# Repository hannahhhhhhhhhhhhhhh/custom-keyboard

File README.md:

# Custom keyboard - A  61-Key Mechanical Keyboard

A custom 60% keyboard that I designed from scratch in KiCad. It has 61 keys, runs on a Seeed XIAO nRF52840 Plus, connects over Bluetooth or USB-C, and uses RMK firmware so you can remap every key with Vial. :3
First time doing stuff with vial and rmk, it was quite a learning curve 

please excuse the lack of 3d models for the above image:  I couldn't add the STEP files to the 3D viewer because my computer keeps crashing when I go to the footprint editor trying to give it a model

## Why I Made This

Honestly, I wanted to design a whole keyboard myself instead of just buying one :D I'm still pretty new to PCB design, and a keyboard seemed like the best way to look at diode matrices, stabilizers other stuff and firmware. I picked the 60% layout because it keeps all the main keys without taking over my whole desk.

I started from the Hack Club Blueprint wireless keyboard guide, which builds a split keyboard. I adapted it into one single board, learned about how matrix worked, did the matrix for 61 keys and figuring out a LOT of pin stuff ;-; (more on that below).

## Specs

- **Layout:** 61-key 60% ANSI (2u Backspace, 2.25u Enter and Left Shift, 2.75u Right Shift, 6.25u Space)
- **Microcontroller:** Seeed XIAO nRF52840 Plus (surface mounted on the PCB)
- **Connectivity:** Bluetooth LE and USB-C
- **Switches:** MX-style, soldered in (no hotswap sockets oops)
- **Matrix:** 5 rows x 14 columns, with one diode per key
- **Stabilizers:** 5 PCB-mount stabilizers
- **Power:** single-cell LiPo soldered to the battery pads, charged over USB-C by the XIAO
- **Firmware:** RMK (Rust), configured with `keyboard.toml` and remappable with Vial
- **Designed in:** KiCad!!!

## How It Works

### The key matrix

A 61-key keyboard would need 61 pins , and no microcontroller has that many so im forced to learn matrix. So the keys are wired as a matrix of 5 rows and 14 columns, which only needs 19 pins. The firmware drives one column at a time and checks which rows see a signal, which tells it exactly which key is pressed.

Every switch has its own diode (SOD-123, the diode footprint from the guide). 

### Why the XIAO nRF52840 Plus

The matrix needs 19 GPIO pins, and the regular XIAO only has 11. The Plus adds extra pads on the back (D11 to D19), so it's the only XIAO that fits this design. It also has Bluetooth, USB-C and a LiPo charger built in, so I swapped to it halfway

Two pin things btw:
- **D16 is unused because** Seeed lists it as the battery voltage sensing pin, so I eventually decided to stay away from it instead of using it as a key column. This also means there's no battery percentage readout, which I'm fine with for now. I added it then had to remove it, which is also why on the pcb the wiring looked a little odd for col11
- **D14 and D15 are NFC pins** by default. The firmware turns on the `nfc-pins-as-gpio` feature so they work as normal key columns.

### Battery

TP1 (GND) and TP2 (VBAT) are the battery pads. Solder a single-cell LiPo to them and the XIAO charges it whenever USB-C is plugged in.

### The PCB

The board has 61 switch footprints in a standard 60% layout, 5 stabilizer footprints (Backspace, Enter, Left Shift, Right Shift and Space), 6 mounting holes, and the two battery pads. and ground plane

## Keymap

The default keymap has two layers. You can change everything in Vial, so this is just where it starts.

- **Base layer:** a standard ANSI 60% layout. Esc is in the top-left corner, and Fn is next to Right Alt.
- **Fn layer:** hold Fn for F1 to F12 on the number row, Fn + Backspace for Delete, Fn + Esc for the backtick, and the arrow keys on I, J, K and L.

## Bill of Materials

All prices are in USD. I'm Canadian, so most of my prices were in CAD and I converted them at about 1 CAD = 0.72 USD.

| Item | Qty | Supplier | Cost/Item (USD) | Total Cost (USD) | Link |
|------|-----|----------|-----------------|------------------|------|
| PCB | 1 | JLCPCB | $34.12 | $34.12 | [link](https://cart.jlcpcb.com/quote) |
| Seeed Studio XIAO nRF52840 Plus | 1 | RobotShop | $10.80 | $10.80 | [link](https://ca.robotshop.com/products/seeed-studio-xiao-nrf52840-plus) |
| YUNZII Milk V2 linear switches (35 per pack) | 2 | Canada Computers | $9.35 | $18.70 | [link](https://www.canadacomputers.com/en/keyboard-switches/285141/yunzii-milk-v2-linear-switch-35-pieces-per-pack-milk-v2.html) |
| ECSiNG stabilizer set (7x 2U and 1x 6.25U) | 1 | Amazon.ca | $9.50 | $9.50 | [link](https://www.amazon.ca/dp/B0FGHP1QQN) |
| SOD-123 diodes (ordered with the PCB) | 61 | JLCPCB | ordered with pcb | $0 | [link](https://cart.jlcpcb.com/quote) |
| Estimated total tax and shipping | 1 | | | $40.47 | |
| | | | **Total (before diodes)** | **$113.59** | |

same list but without the key switches cost is in [`BOM.csv`](BOM.csv). (I already bought the key switches myself so didn't count that in bom. Keycaps aren't in this list yet because I'm still deciding on a set, so they aren't in the total.

### About the shipping ;-;

ok so I have to explain the shipping because it looks kind of crazy. I'm Canadian, and almost every store I could order from charges around $20 in shipping per order, no matter how small the order is FOR SOME REASON. To avoid paying that yet again, I ordered the diodes together with the PCB from JLCPCB instead of buying them from another store. Even with that, the tax and shipping for the rest of the parts comes to about $40.47 CAD (around $29.14 USD), and that part was unavoidable. So over a quarter of my total is just shipping q-p

## Firmware Flashing Guide

The firmware is built with [RMK](https://rmk.rs) and lives in the `firmware/` folder: `keyboard.toml` has the pins, layout and keymap, and `vial.json` has the layout for Vial.

### What you need

- A USB-C **data** cable (some cables only charge)
- The firmware as a `.uf2` file (see step 1)

### 1. Get the firmware

**Option A: GitHub Actions ** 
1. Open the **Actions** tab of this repo.
2. Click the latest successful run.
3. Download the firmware from **Artifacts** and unzip it. The `.uf2` file is inside.

**Option B:just do it**
1. Install Rust and `cargo-make`: `cargo install --force cargo-make`
2. In the `firmware/` folder, run `cargo make uf2 --release`

### 2. Put the keyboard in bootloader mode

1. Plug the keyboard into your computer over USB-C.
2. **Double-tap** the small reset button on the XIAO, quickly.
3. A new USB drive appears on your computer.

### 3. Flash it

Drag the `.uf2` file onto the new drive. The drive disappears and the keyboard reboots. That's it, you're done! (If macOS shows an error while copying, you can ignore it.)

### 4. Connect

- **USB:** it works as soon as it's plugged in.
- **Bluetooth:** pair with **keyboard:3** in your computer's Bluetooth settings.
- **Remapping:** plug it in over USB and open Vial to change keys and layers.

### Troubleshooting

| Problem | Fix |
|---------|-----|
| The USB drive doesn't appear | Double-tap the reset button faster, and try a different USB-C cable (it must be a data cable). |
| Two columns of keys do nothing | Those are the NFC pins (COL7 and COL9). Make sure `nfc-pins-as-gpio` is enabled on the `embassy-nrf` dependency in `Cargo.toml`. |
| Keys type the wrong thing | Open Vial and check the keymap. The layout in `vial.json` has to match `keyboard.toml` tho. |

## What I Learned

- A diode matrix is way less scary than it looks :D
- Not every pin on a microcontroller is a normal GPIO pin
- Reading the ERC errors one by one is much better than panicking at the number ;-;
- Getting the pin names right across the schematic, the footprints, the firmware and Vial is the hardest part of the whole project :pain:

## Repository Structure

```
.
├── README.md
├── BOM.csv
├── images/
│   ├── schematic.png
│   ├── pcb.png
│   └── pcb-3d.png
├── kicad/
│   ├── keyboard.kicad_pro
│   ├── keyboard.kicad_sch
│   └── keyboard.kicad_pcb
├── production/
│   ├── keyboard.zip
│   ├── bom.csv
│   ├── positions.csv
│   └── netlist.ipc
├── firmware/
│   ├── Cargo.toml
│   ├── keyboard.toml
│   ├── main.rs
│   ├── memory.x
│   └── vial.json
└── .github/workflows/
```

## Made For

Hack Club :3

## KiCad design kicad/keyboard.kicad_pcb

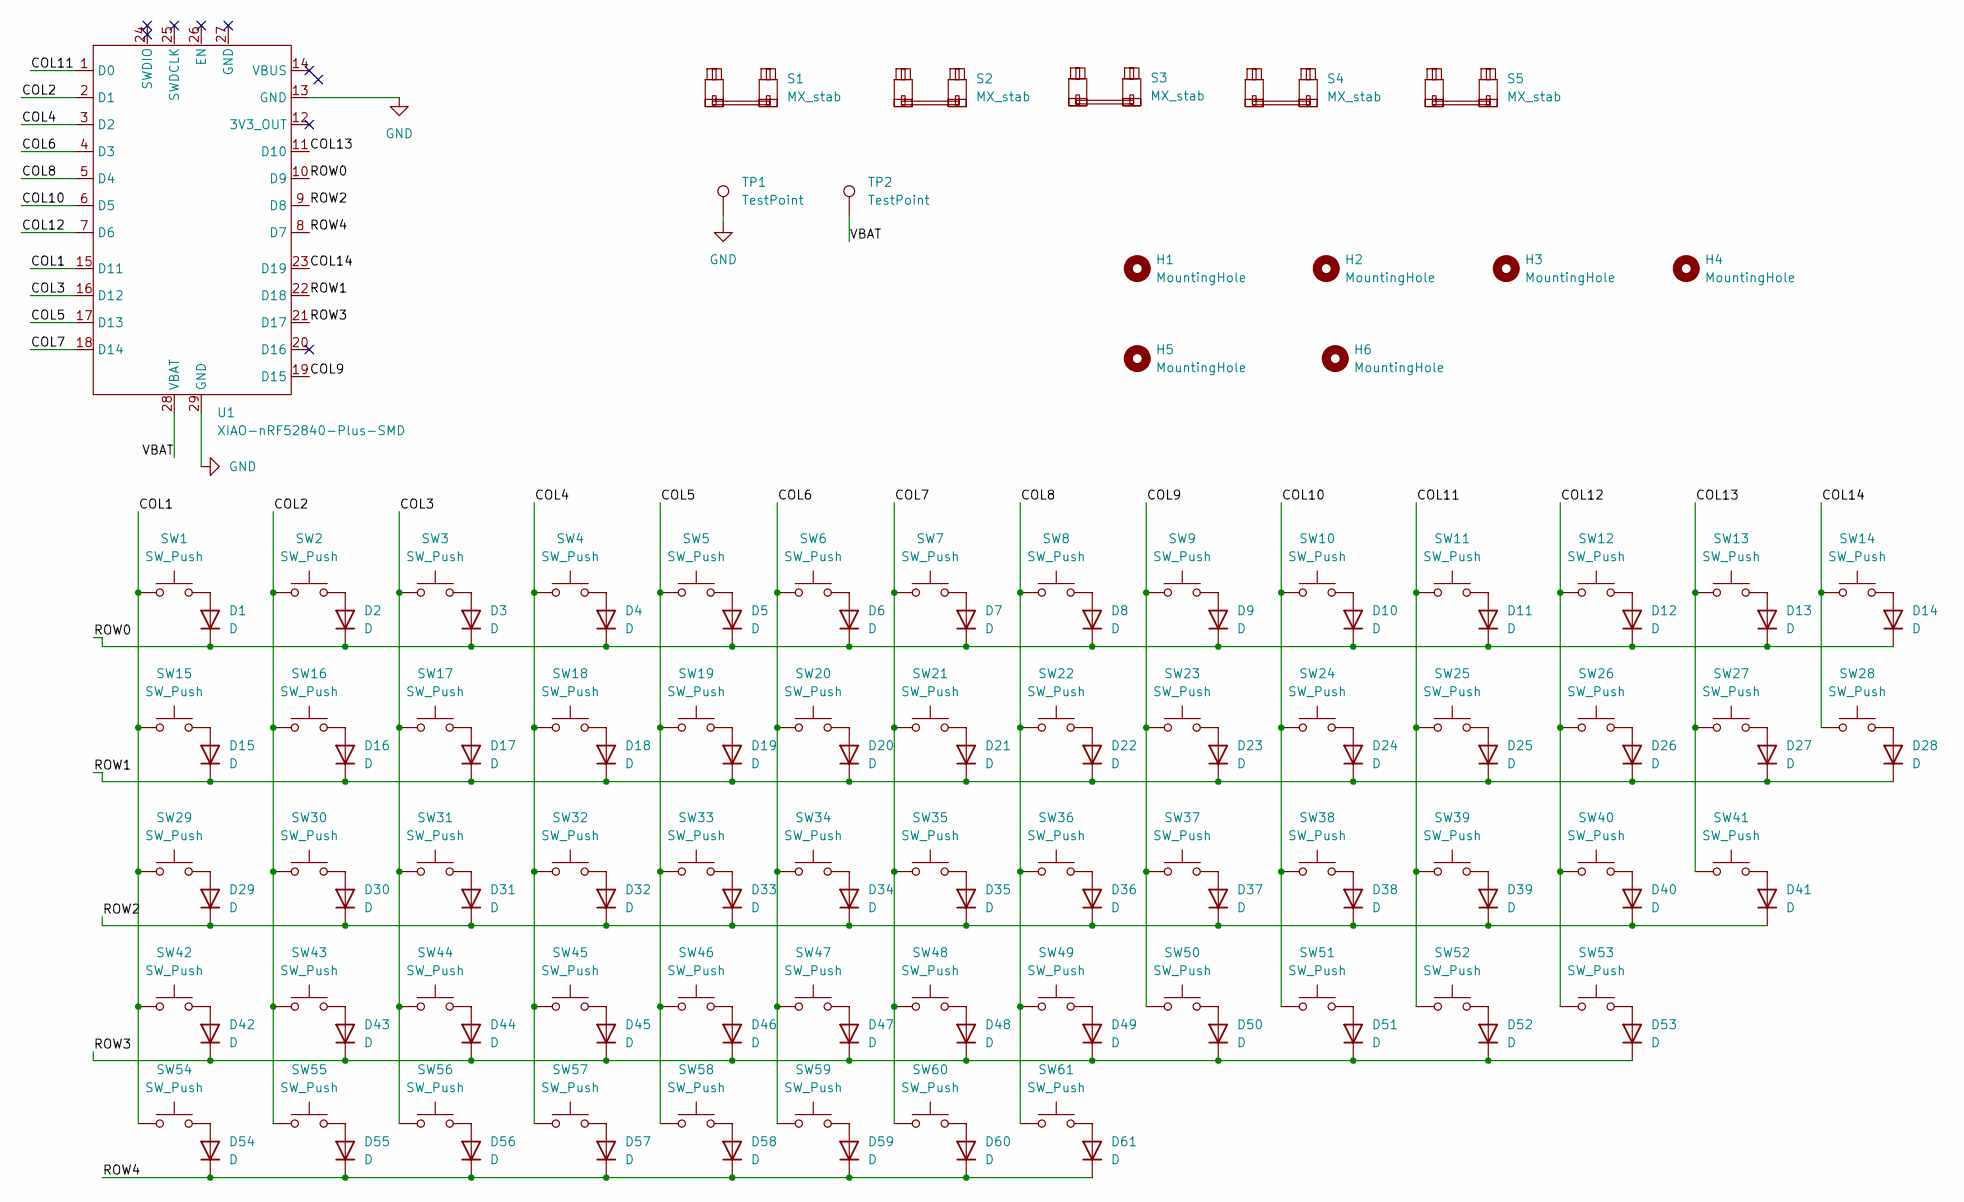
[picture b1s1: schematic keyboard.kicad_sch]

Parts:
D1, D2, D3, D4, D5, D6, D7, D8, D9, D10, D11, D12, D13, D14, D15, D16, D17, D18, D19, D20, D21, D22, D23, D24, D25, D26, D27, D28, D29, D30, D31, D32, D33, D34, D35, D36, D37, D38, D39, D40, D41, D42, D43, D44, D45, D46, D47, D48, D49, D50, D51, D52, D53, D54, D55, D56, D57, D58, D59, D60, D61: D; D_SOD-123
H1, H2, H3, H4, H5, H6: MountingHole; MountingHole_2.2mm_M2
S1, S2, S3, S4: MX_stab; STAB_MX_P_2u
S5: MX_stab; STAB_MX_P_6.25u
SW1, SW2, SW3, SW4, SW5, SW6, SW7, SW8, SW9, SW10, SW11, SW12, SW13, SW16, SW17, SW18, SW19, SW20, SW21, SW22, SW23, SW24, SW25, SW26, SW27, SW30, SW31, SW32, SW33, SW34, SW35, SW36, SW37, SW38, SW39, SW40, SW43, SW44, SW45, SW46, SW47, SW48, SW49, SW50, SW51, SW52: SW_Push; SW_Cherry_MX_1.00u_PCB
SW14: SW_Push; SW_Cherry_MX_2.00u_PCB
SW15, SW28: SW_Push; SW_Cherry_MX_1.50u_PCB
SW29: SW_Push; SW_Cherry_MX_1.75u_PCB
SW41, SW42: SW_Push; SW_Cherry_MX_2.25u_PCB
SW53: SW_Push; SW_Cherry_MX_2.75u_PCB
SW54, SW55, SW56, SW58, SW59, SW60, SW61: SW_Push; SW_Cherry_MX_1.25u_PCB
SW57: SW_Push; SW_Cherry_MX_6.25u_PCB
TP1, TP2: TestPoint; TestPoint_Bridge_Pitch3.81mm_Drill1.3mm
U1: XIAO-nRF52840-Plus-SMD

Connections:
/COL1: SW1.1, SW15.1, SW29.1, SW42.1, SW54.1, U1.15 (D11)
/COL2: SW2.1, SW16.1, SW30.1, SW43.1, SW55.1, U1.2 (D1)
/COL3: SW3.1, SW17.1, SW31.1, SW44.1, SW56.1, U1.16 (D12)
/COL4: SW4.1, SW18.1, SW32.1, SW45.1, SW57.1, U1.3 (D2)
/COL5: SW5.1, SW19.1, SW33.1, SW46.1, SW58.1, U1.17 (D13)
/COL6: SW6.1, SW20.1, SW34.1, SW47.1, SW59.1, U1.4 (D3)
/COL7: SW7.1, SW21.1, SW35.1, SW48.1, SW60.1, U1.18 (D14)
/COL8: SW8.1, SW22.1, SW36.1, SW49.1, SW61.1, U1.5 (D4)
/COL9: SW9.1, SW23.1, SW37.1, SW50.1, U1.19 (D15)
/COL10: SW10.1, SW24.1, SW38.1, SW51.1, U1.6 (D5)
/COL11: SW11.1, SW25.1, SW39.1, SW52.1, U1.1 (D0)
/COL12: SW12.1, SW26.1, SW40.1, SW53.1, U1.7 (D6)
/COL13: SW13.1, SW27.1, SW41.1, U1.11 (D10)
/COL14: SW14.1, SW28.1, U1.23 (D19)
/ROW0: D1.1 (K), D2.1 (K), D3.1 (K), D4.1 (K), D5.1 (K), D6.1 (K), D7.1 (K), D8.1 (K), D9.1 (K), D10.1 (K), D11.1 (K), D12.1 (K), D13.1 (K), D14.1 (K), U1.10 (D9)
/ROW1: D15.1 (K), D16.1 (K), D17.1 (K), D18.1 (K), D19.1 (K), D20.1 (K), D21.1 (K), D22.1 (K), D23.1 (K), D24.1 (K), D25.1 (K), D26.1 (K), D27.1 (K), D28.1 (K), U1.22 (D18)
/ROW2: D29.1 (K), D30.1 (K), D31.1 (K), D32.1 (K), D33.1 (K), D34.1 (K), D35.1 (K), D36.1 (K), D37.1 (K), D38.1 (K), D39.1 (K), D40.1 (K), D41.1 (K), U1.9 (D8)
/ROW3: D42.1 (K), D43.1 (K), D44.1 (K), D45.1 (K), D46.1 (K), D47.1 (K), D48.1 (K), D49.1 (K), D50.1 (K), D51.1 (K), D52.1 (K), D53.1 (K), U1.21 (D17)
/ROW4: D54.1 (K), D55.1 (K), D56.1 (K), D57.1 (K), D58.1 (K), D59.1 (K), D60.1 (K), D61.1 (K), U1.8 (D7)
/VBAT: TP2.1 (1_1), U1.28 (VBAT)
GND: TP1.1 (1_1), U1.13 (GND), U1.29 (GND)
unnamed: D1.2 (A), SW1.2
unnamed: D2.2 (A), SW2.2
unnamed: D3.2 (A), SW3.2
unnamed: D4.2 (A), SW4.2
unnamed: D5.2 (A), SW5.2
unnamed: D6.2 (A), SW6.2
unnamed: D7.2 (A), SW7.2
unnamed: D8.2 (A), SW8.2
unnamed: D9.2 (A), SW9.2
unnamed: D10.2 (A), SW10.2
unnamed: D11.2 (A), SW11.2
unnamed: D12.2 (A), SW12.2
unnamed: D13.2 (A), SW13.2
unnamed: D14.2 (A), SW14.2
unnamed: D15.2 (A), SW15.2
unnamed: D16.2 (A), SW16.2
unnamed: D17.2 (A), SW17.2
unnamed: D18.2 (A), SW18.2
unnamed: D19.2 (A), SW19.2
unnamed: D20.2 (A), SW20.2
unnamed: D21.2 (A), SW21.2
unnamed: D22.2 (A), SW22.2
unnamed: D23.2 (A), SW23.2
unnamed: D24.2 (A), SW24.2
unnamed: D25.2 (A), SW25.2
unnamed: D26.2 (A), SW26.2
unnamed: D27.2 (A), SW27.2
unnamed: D28.2 (A), SW28.2
unnamed: D29.2 (A), SW29.2
unnamed: D30.2 (A), SW30.2
unnamed: D31.2 (A), SW31.2
unnamed: D32.2 (A), SW32.2
unnamed: D33.2 (A), SW33.2
unnamed: D34.2 (A), SW34.2
unnamed: D35.2 (A), SW35.2
unnamed: D36.2 (A), SW36.2
unnamed: D37.2 (A), SW37.2
unnamed: D38.2 (A), SW38.2
unnamed: D39.2 (A), SW39.2
unnamed: D40.2 (A), SW40.2
unnamed: D41.2 (A), SW41.2
unnamed: D42.2 (A), SW42.2
unnamed: D43.2 (A), SW43.2
unnamed: D44.2 (A), SW44.2
unnamed: D45.2 (A), SW45.2
unnamed: D46.2 (A), SW46.2
unnamed: D47.2 (A), SW47.2
unnamed: D48.2 (A), SW48.2
unnamed: D49.2 (A), SW49.2
unnamed: D50.2 (A), SW50.2
unnamed: D51.2 (A), SW51.2
unnamed: D52.2 (A), SW52.2
unnamed: D53.2 (A), SW53.2
unnamed: D54.2 (A), SW54.2
unnamed: D55.2 (A), SW55.2
unnamed: D56.2 (A), SW56.2
unnamed: D57.2 (A), SW57.2
unnamed: D58.2 (A), SW58.2
unnamed: D59.2 (A), SW59.2
unnamed: D60.2 (A), SW60.2
unnamed: D61.2 (A), SW61.2

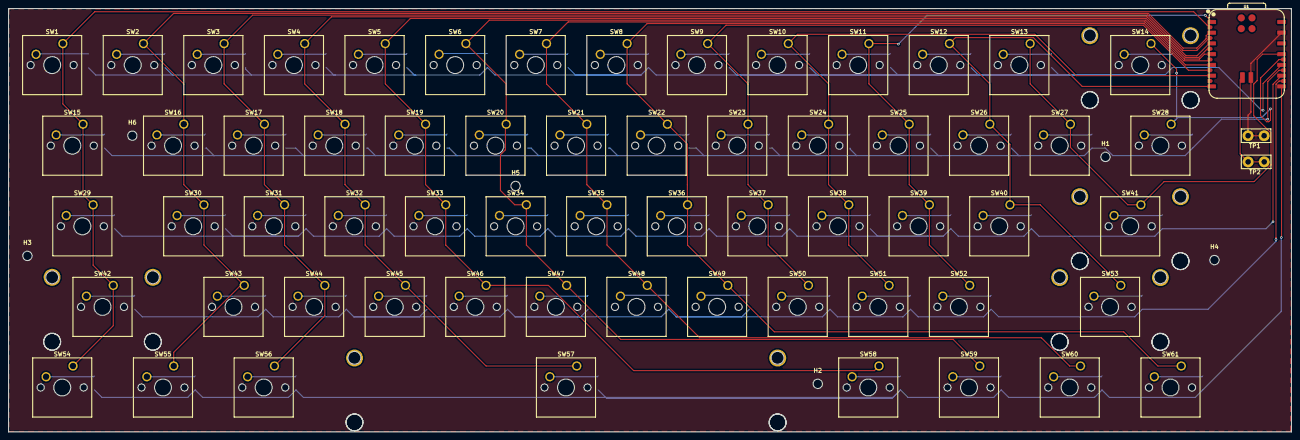
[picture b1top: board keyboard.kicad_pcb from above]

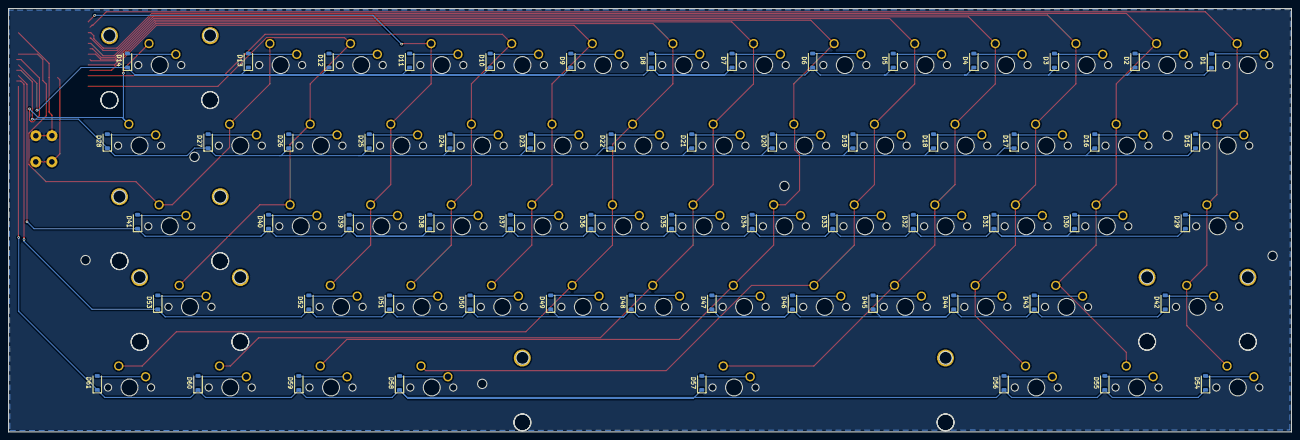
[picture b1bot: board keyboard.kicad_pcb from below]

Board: 2 copper layers, 303.2 x 100.0 mm, 136 parts (61 on the bottom side), 82 nets.
